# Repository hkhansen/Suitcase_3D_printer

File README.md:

# Suitcase 3D printer
This custom 3D printer is designed to fit in a small pelican suitcase from [Harald Nyborg](https://www.harald-nyborg.dk/mitsutomo-kuffert-111-x-192-x-232-mm).
All of the mechanical parts are either 3D printed or leftovers from an old Tevo Tarantula 3D printer.

## THIS IS A WORK IN PROGRESS

**The following needs to be finished/implemented**
- Electronics need to be finished and a electronics box is needed.
- A power supply is needed.
- The Klipper firmware needs to be prepared on the controller.

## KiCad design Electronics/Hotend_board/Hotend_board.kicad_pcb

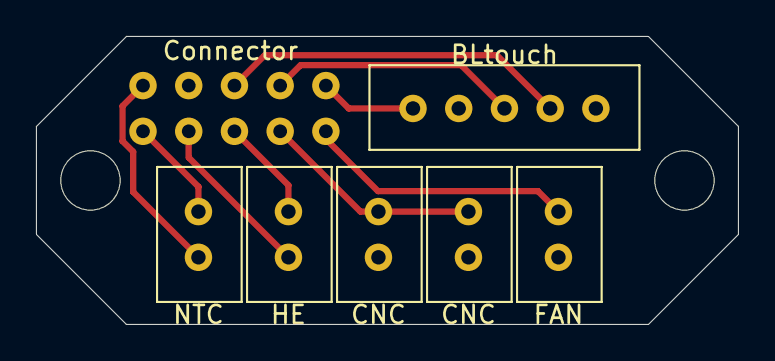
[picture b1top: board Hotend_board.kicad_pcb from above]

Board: 2 copper layers, 39.0 x 16.0 mm, 7 parts (0 on the bottom side), 10 nets.

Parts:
BLtouch: 1x5-header; JST_XH_5
CNC: 1x2-header; JST_XH_2
CNC#2: 1x2-header; JST_XH_2
Connector: 2x5-header; 2x5_pin
FAN: 1x2-header; JST_XH_2
HE: 1x2-header; JST_XH_2
NTC: 1x2-header; JST_XH_2

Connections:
+5V: BLtouch.4, Connector.6
/CNC_fan: CNC.1, CNC#2.1, Connector.7
/H1: Connector.5, HE.1
/H2: Connector.3, HE.2
/HE_fan: Connector.9, FAN.1
/NTC1: Connector.1, NTC.1
/NTC2: Connector.2, NTC.2
/Servo: BLtouch.3, Connector.8
/Z-: BLtouch.1, Connector.10
GND: BLtouch.2, BLtouch.5, CNC.2, CNC#2.2, Connector.4, FAN.2

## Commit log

2023-02-28 Re-upload
